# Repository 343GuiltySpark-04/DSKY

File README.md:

# DSKY

## This is a project where I make a replica of the DSKY (DiSplay and Keyboard assemblY) that works with ReEntry: an orbital simulator.

I am planning to sell these replicas. I have made functional prototypes of the display and keyboard, i just need to design pcb's to merge it all together, which i am currently doing.

## Guide on hooking up the PCB and installing the software

Preperation: hookup your arduino to your PC, download the repo in zip format and extract it, and enable the AGC output function in teh reentry settings (at the bottom).

# Step one: install python

Go to this link:

https://realpython.com/installing-python/

And follow the guide for your respective OS.

# Step two: edit the port.

Right click the JSON_export file, and edit with IDLE. First, check to what port your arduino is plugged in.
You can find the device manager by searching for it in Start. Then select Ports to display the list of ports. It should say Arduino (COMX).

Now, remember what number is behind the port. Go back to the script and edit where it says COM3 into what port yours is (COM1, COM2, etc).

# Step 3: Upload the code onto the arduino

Install the arduino IDE from the arduino website. Next, open the display.ino file from the display folder in the arduino IDE. Now, click on Tools > ports > and select
your correct port (the one you put in the script). Now, click on the upload button in  the top left. When its done, you can close the IDE. To use it now, you can run the python script in IDLE.

# Step 4: Hooking up the PCB

*WIP*

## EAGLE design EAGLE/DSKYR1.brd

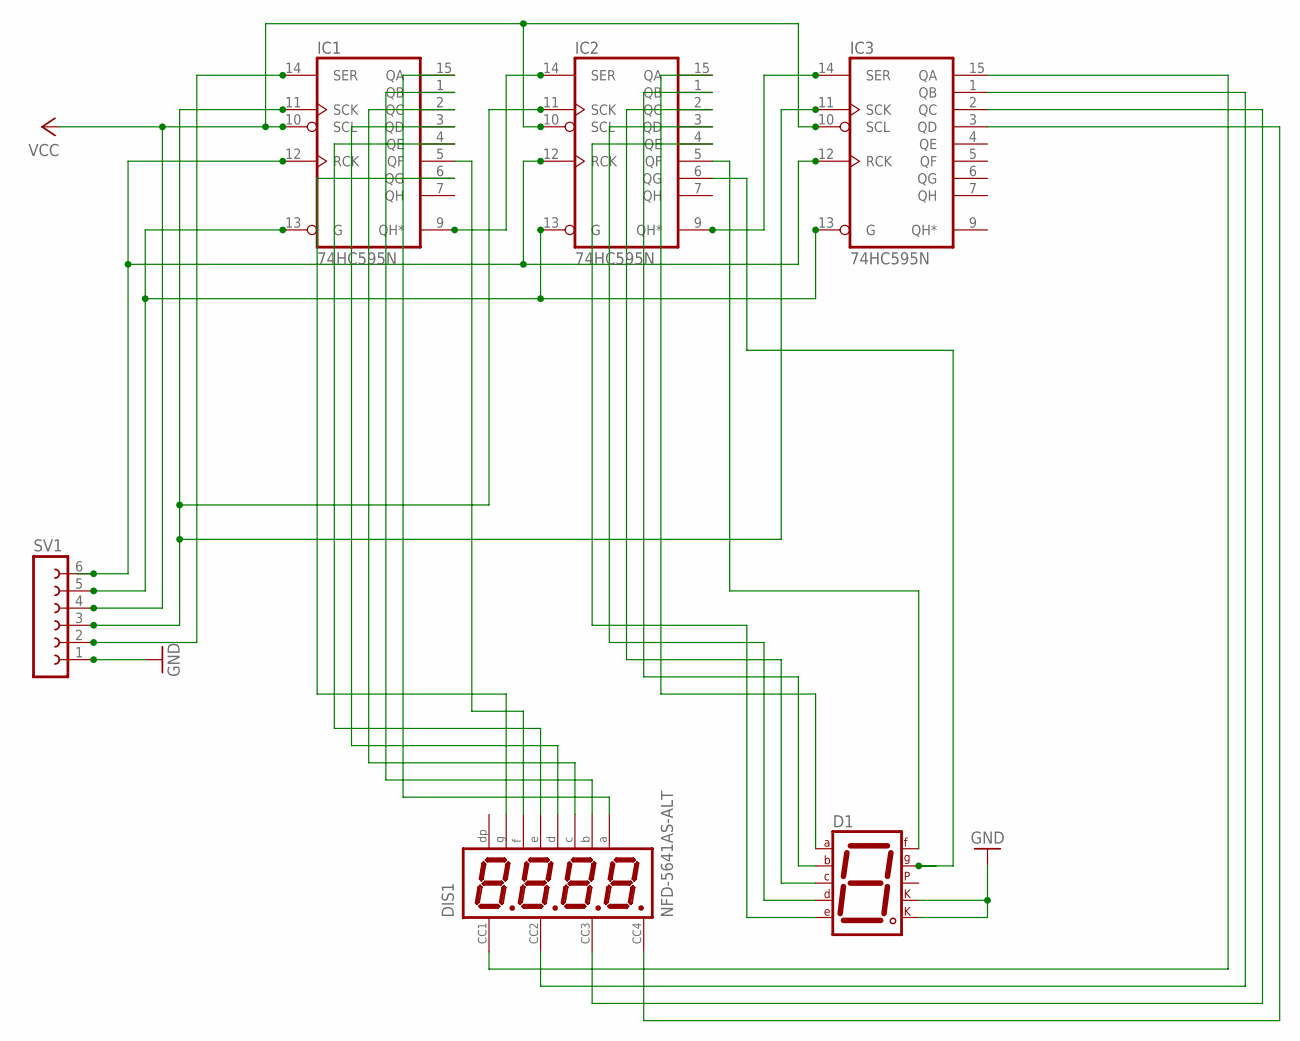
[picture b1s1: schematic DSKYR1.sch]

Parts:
D1: 7SEG-CK; 7SEG-13
DIS1: NFD-5641AS-ALT; NFD-5641
IC1, IC2, IC3: 74HC595N; DIL16
SV1: FE06-1; FE06

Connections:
GND: D1.3 (CK1), D1.8 (CK2), IC1.8 (GND), IC2.8 (GND), IC3.8 (GND), SV1.1
unnamed: IC1.12 (RCK), IC2.12 (RCK), IC3.12 (RCK), SV1.6
unnamed: DIS1.P$10, IC1.5 (QF)
unnamed: DIS1.P$5, IC1.6 (QG)
unnamed: IC1.13 (G), IC2.13 (G), IC3.13 (G), SV1.5
unnamed: IC1.14 (SER), SV1.2
unnamed: IC1.9 (QH*), IC2.14 (SER)
unnamed: IC1.11 (SCK), IC2.11 (SCK), IC3.11 (SCK), SV1.3
unnamed: IC2.9 (QH*), IC3.14 (SER)
unnamed: DIS1.P$11, IC1.15 (QA)
unnamed: DIS1.P$7, IC1.1 (QB)
unnamed: DIS1.P$4, IC1.2 (QC)
unnamed: DIS1.P$2, IC1.3 (QD)
unnamed: DIS1.P$1, IC1.4 (QE)
unnamed: D1.7 (A), IC2.15 (QA)
unnamed: D1.6 (B), IC2.1 (QB)
unnamed: D1.4 (C), IC2.2 (QC)
unnamed: D1.2 (D), IC2.3 (QD)
unnamed: D1.1 (E), IC2.4 (QE)
unnamed: D1.9 (F), IC2.5 (QF)
unnamed: D1.10 (G), IC2.6 (QG)
unnamed: DIS1.P$12, IC3.15 (QA)
unnamed: DIS1.P$9, IC3.1 (QB)
unnamed: DIS1.P$8, IC3.2 (QC)
unnamed: DIS1.P$6, IC3.3 (QD)
VCC: IC1.10 (SCL), IC1.16 (VCC), IC2.10 (SCL), IC2.16 (VCC), IC3.10 (SCL), IC3.16 (VCC), SV1.4

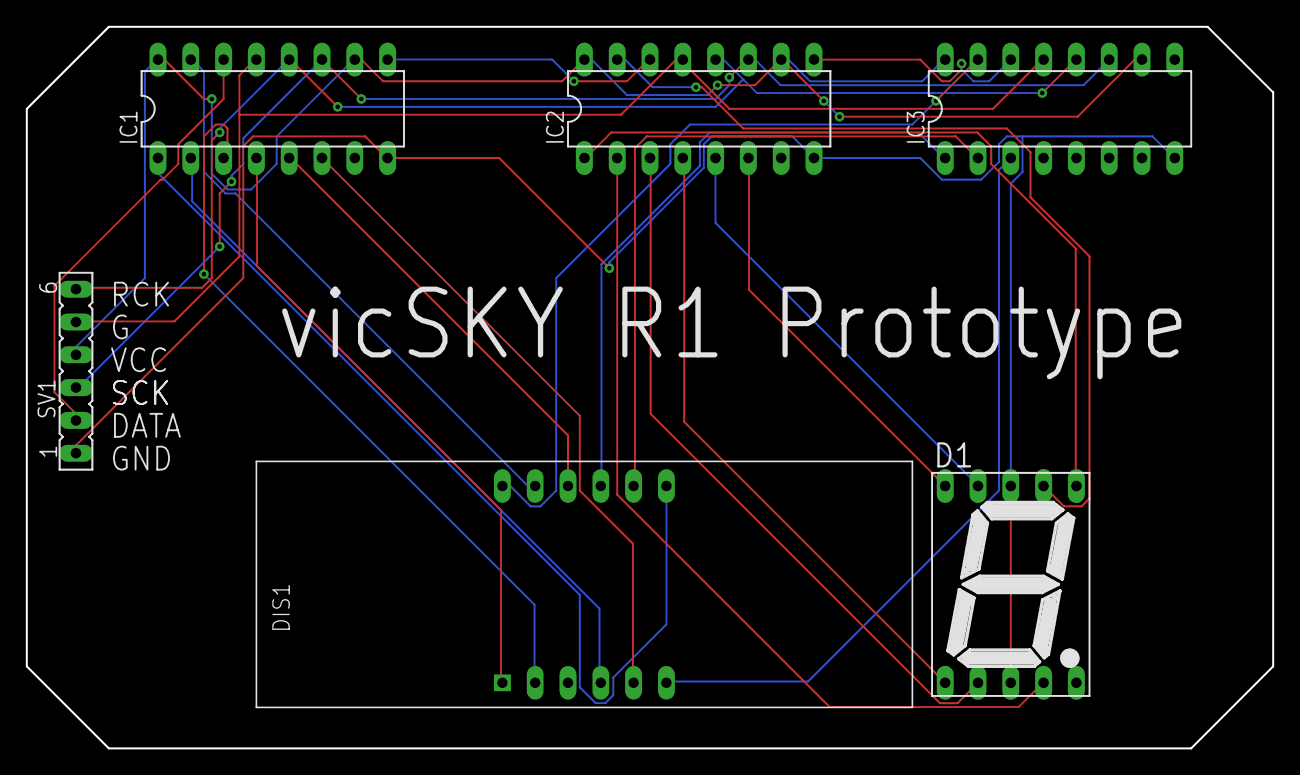
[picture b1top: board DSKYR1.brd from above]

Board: 2 copper layers, 96.5 x 55.9 mm, 6 parts (0 on the bottom side), 26 nets.

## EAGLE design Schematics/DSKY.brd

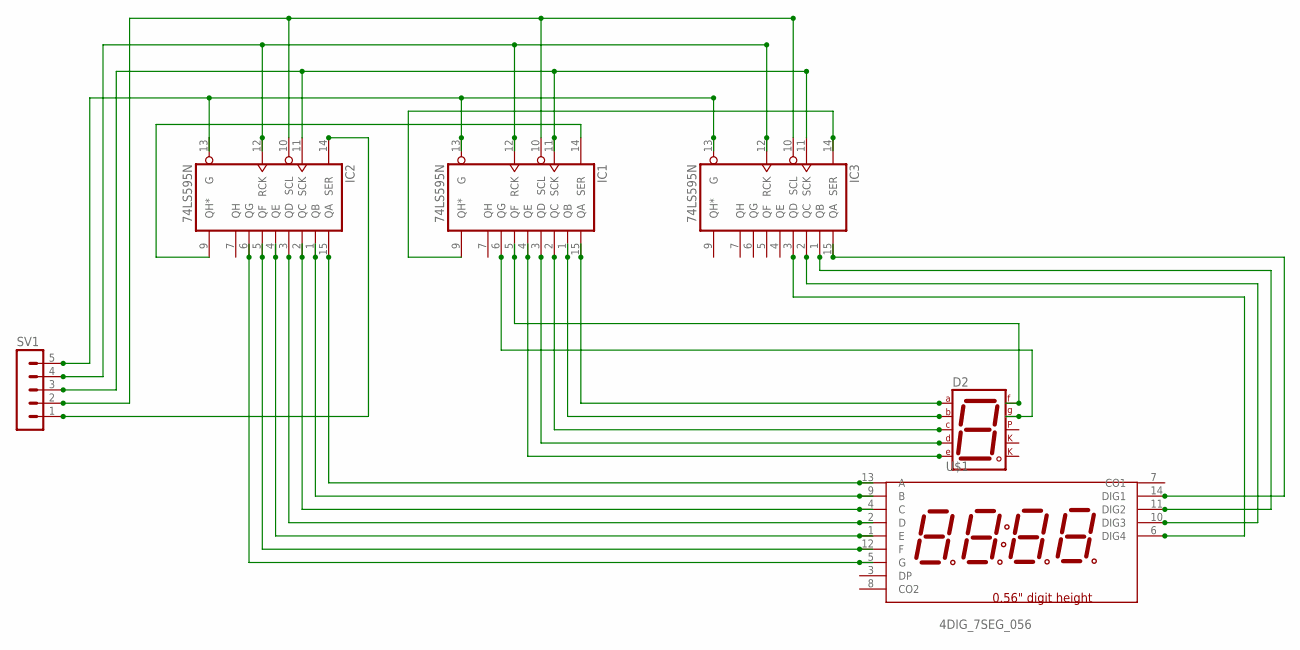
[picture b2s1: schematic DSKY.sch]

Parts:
D2: 7SEG-CK; 7SEG-13
IC1, IC2, IC3: 74LS595N; DIL16
SV1: MA05-1
U$1: 4DIG_7SEG_056

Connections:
GND: IC1.8 (GND), IC2.8 (GND), IC3.8 (GND)
unnamed: IC2.15 (QA), U$1.13 (A)
unnamed: IC2.1 (QB), U$1.9 (B)
unnamed: IC2.2 (QC), U$1.4 (C)
unnamed: IC2.3 (QD), U$1.2 (D)
unnamed: IC2.4 (QE), U$1.1 (E)
unnamed: IC2.5 (QF), U$1.12 (F)
unnamed: IC2.6 (QG), U$1.5 (G)
unnamed: D2.7 (A), IC1.15 (QA)
unnamed: D2.6 (B), IC1.1 (QB)
unnamed: D2.4 (C), IC1.2 (QC)
unnamed: D2.2 (D), IC1.3 (QD)
unnamed: D2.1 (E), IC1.4 (QE)
unnamed: D2.9 (F), IC1.5 (QF)
unnamed: D2.10 (G), IC1.6 (QG)
unnamed: IC3.15 (QA), U$1.14 (DIG1)
unnamed: IC3.1 (QB), U$1.11 (DIG2)
unnamed: IC3.2 (QC), U$1.10 (DIG3)
unnamed: IC3.3 (QD), U$1.6 (DIG4)
unnamed: IC1.13 (G), IC2.13 (G), IC3.13 (G), SV1.5
unnamed: IC1.14 (SER), IC2.9 (QH*)
unnamed: IC1.9 (QH*), IC3.14 (SER)
unnamed: IC1.12 (RCK), IC2.12 (RCK), IC3.12 (RCK), SV1.4
unnamed: IC1.11 (SCK), IC2.11 (SCK), IC3.11 (SCK), SV1.3
unnamed: IC1.10 (SCL), IC2.10 (SCL), IC3.10 (SCL), SV1.2
unnamed: IC2.14 (SER), SV1.1
VCC: IC1.16 (VCC), IC2.16 (VCC), IC3.16 (VCC)

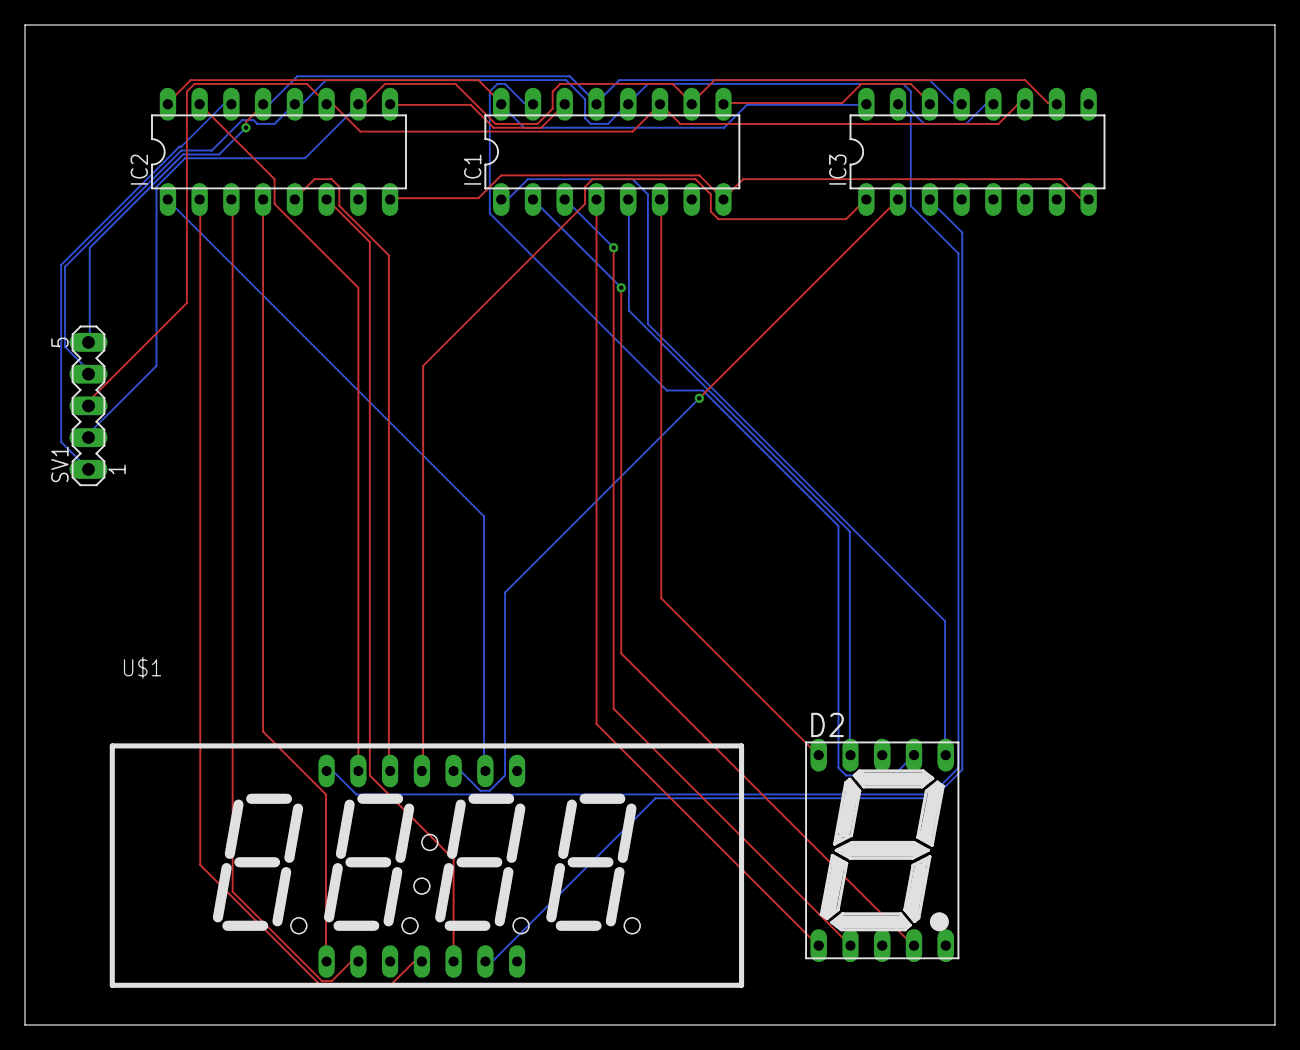
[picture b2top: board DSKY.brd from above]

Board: 2 copper layers, 100.0 x 80.0 mm, 6 parts (0 on the bottom side), 27 nets.

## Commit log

2020-11-08 Update gay.txt
    look in file
2020-12-22 Remove weird shit
2020-12-27 Reorganize, and add EAGLE files
2020-12-27 Update shit
2020-12-27 Update BRD
2021-01-12 Rework PCB and schematic
2021-01-15 Update guide, finalize gerber files
2021-01-22 Rewrite display.iino
    save ur code u stupid fuck
2021-01-22 Update display.ino
    pushed the wrong file lol
2021-01-22 Connect ground lines of R1D5
